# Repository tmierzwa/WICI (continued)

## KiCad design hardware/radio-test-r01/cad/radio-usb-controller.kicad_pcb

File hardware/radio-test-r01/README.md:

# WICI R01.3: kontroler w archiwum

**Status: ARCHIWUM. Kontrolera nie buduje się ani jako stanowiska, ani jako modemu; źródła pozostają do wglądu.**

W wersji 0.5 R01.3 nie jest kontrolerem stacji: STM32F103 ma za mało pamięci na stos Reticulum. Pomiary profilu P1 i próby T1–T4 wykonuje się na [stanowisku deweloperskim](../dev-bench/README.md) z płytek rozwojowych i modułów producentów, a pierwszą drukowaną płytką projektu jest płytka stacji R02 z [wymagań w specyfikacji elektroniki](../../docs/spec/elektronika.md). Z R01.3 przechodzą do R02 tylko wnioski toru RF z [warunków przed zamówieniem](przed-produkcja.md); kontrakt USB/KISS nie obowiązuje.

Przegląd elektryczny wskazał problem USB suspend: Y1 ma stale włączony zegar, więc parametry katalogowe nie gwarantują budżetu 2,5 mA przy zasilaniu z VBUS. Poprawka wymagałaby nowej rewizji CAD; po archiwizacji nie jest planowana.

Repozytorium zawiera edytowalne pliki kontrolera USB w KiCad. Tor radiowy CC1120 był osobnym modułem opartym na referencji TI; na stanowisku deweloperskim zastępuje go gotowy moduł TI CC1120EM-868-915.

| Plik | Zawartość |
|---|---|
| [Projekt KiCad](cad/radio-usb-controller.kicad_pro) | Schemat, PCB 70 × 55 mm, cztery warstwy, lokalne biblioteki |
| [Schemat](cad/radio-usb-controller.kicad_sch) | USB, STM32, zegar, EEPROM, programator, interfejs radia |
| [PCB](cad/radio-usb-controller.kicad_pcb) | Rozmieszczenie i poprowadzone połączenia |
| [BOM](bom.csv) | MPN i producenci; 39 pozycji montażowych na jeden kontroler; TP1–TP7 to pola pomiarowe |
| [Połączenia](polaczenia.md) | Numery pinów i przewód do referencji TI |
| [Uruchomienie](uruchomienie.md) | Kolejne pomiary oraz warunki przerwania próby |
| [Otwarte sprawy](przed-produkcja.md) | Przeszkody przed zamówieniem |
| [Zmiany R01.3](zmiany-R01-3.md) | Stos 1,6 mm, rewizja, MPN i zweryfikowane eksporty |
| [Paczka produkcyjna](fabrication/wici-controller-R01.3.zip) | Kandydat: Gerbery, wiercenia i pliki montażowe samego kontrolera |
| [Zmiany R01.2](zmiany-R01-2.md) | Zasilanie 0,5 mm, przelotki, otwory i bezpiecznik |
| [Wydruk 1:1](mechanika-1-do-1.pdf) | Fizyczna kontrola USB-B, SW1 i IDC; druk 100%, bez odbicia |
| [Weryfikacja](checks/status.json) | Wyniki, zakres i ograniczenia kontroli |

Kontroler: ERC 0, DRC 0, brakujących połączeń 0, różnic PCB–schemat 0. Raporty pochodzą z KiCad 10.0.6, z jawnymi regułami w pliku `.kicad_dru` i wypełnionymi polami miedzi. Kontrola zachowuje domyślne pominięcia KiCad wymienione w JSON; nie jest pełnym dowodem poprawności układu.

**Nie ma jeszcze gotowego modemu do użycia.** Nie ma firmware, zaakceptowanego zegara RF, zweryfikowanego pliku produkcyjnego RF ani wyników fizycznych prób. DRC nie sprawdza impedancji USB, dopasowania anteny, jakości lutowania ani zasięgu. Zasięg 1 km jest celem, który wymaga pomiaru.

Wygenerowano i sprawdzono paczkę Gerberów samego kontrolera R01.3. Nie sprawdzono fizycznego dopasowania złączy. Stos producenta jest zapisany w PCB; ocena impedancji USB i kwalifikacja układu pozostają otwarte. Lokalny folder `reference-private` zawiera materiały producenta i niezaakceptowaną konwersję oznaczoną `NOT-FOR-FAB`; folder nie jest częścią repozytorium.

[Odtworzenie kontroli i paczek](odtworzenie.md). [Środowisko narzędzi](../../docs/development.md).

Otwórz plik projektu w KiCad 10.0.6. Nie trzeba instalować dodatkowych bibliotek elementów. [Licencje](LICENSES.md) rozdzielają własny projekt od materiałów producentów.

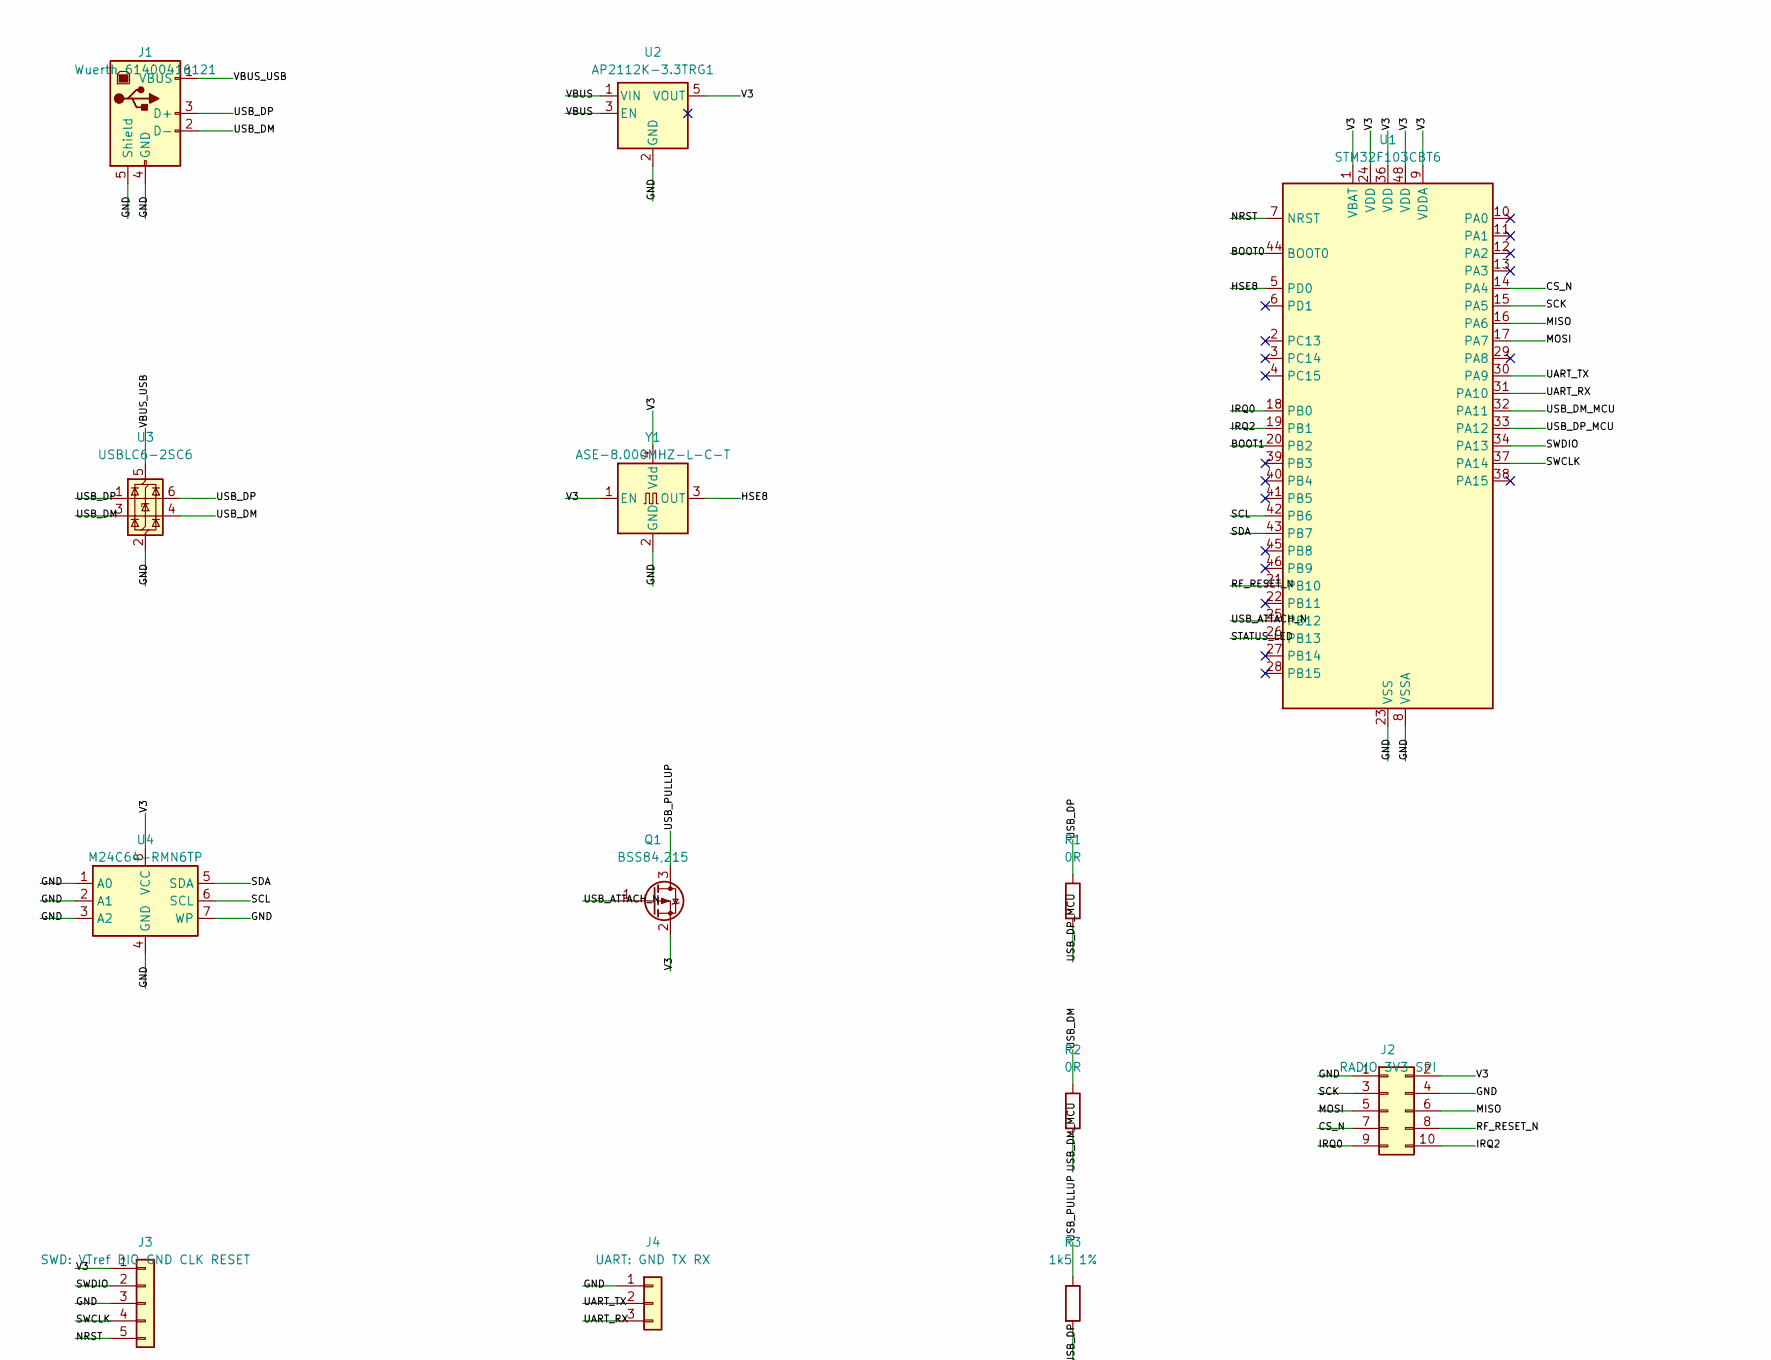
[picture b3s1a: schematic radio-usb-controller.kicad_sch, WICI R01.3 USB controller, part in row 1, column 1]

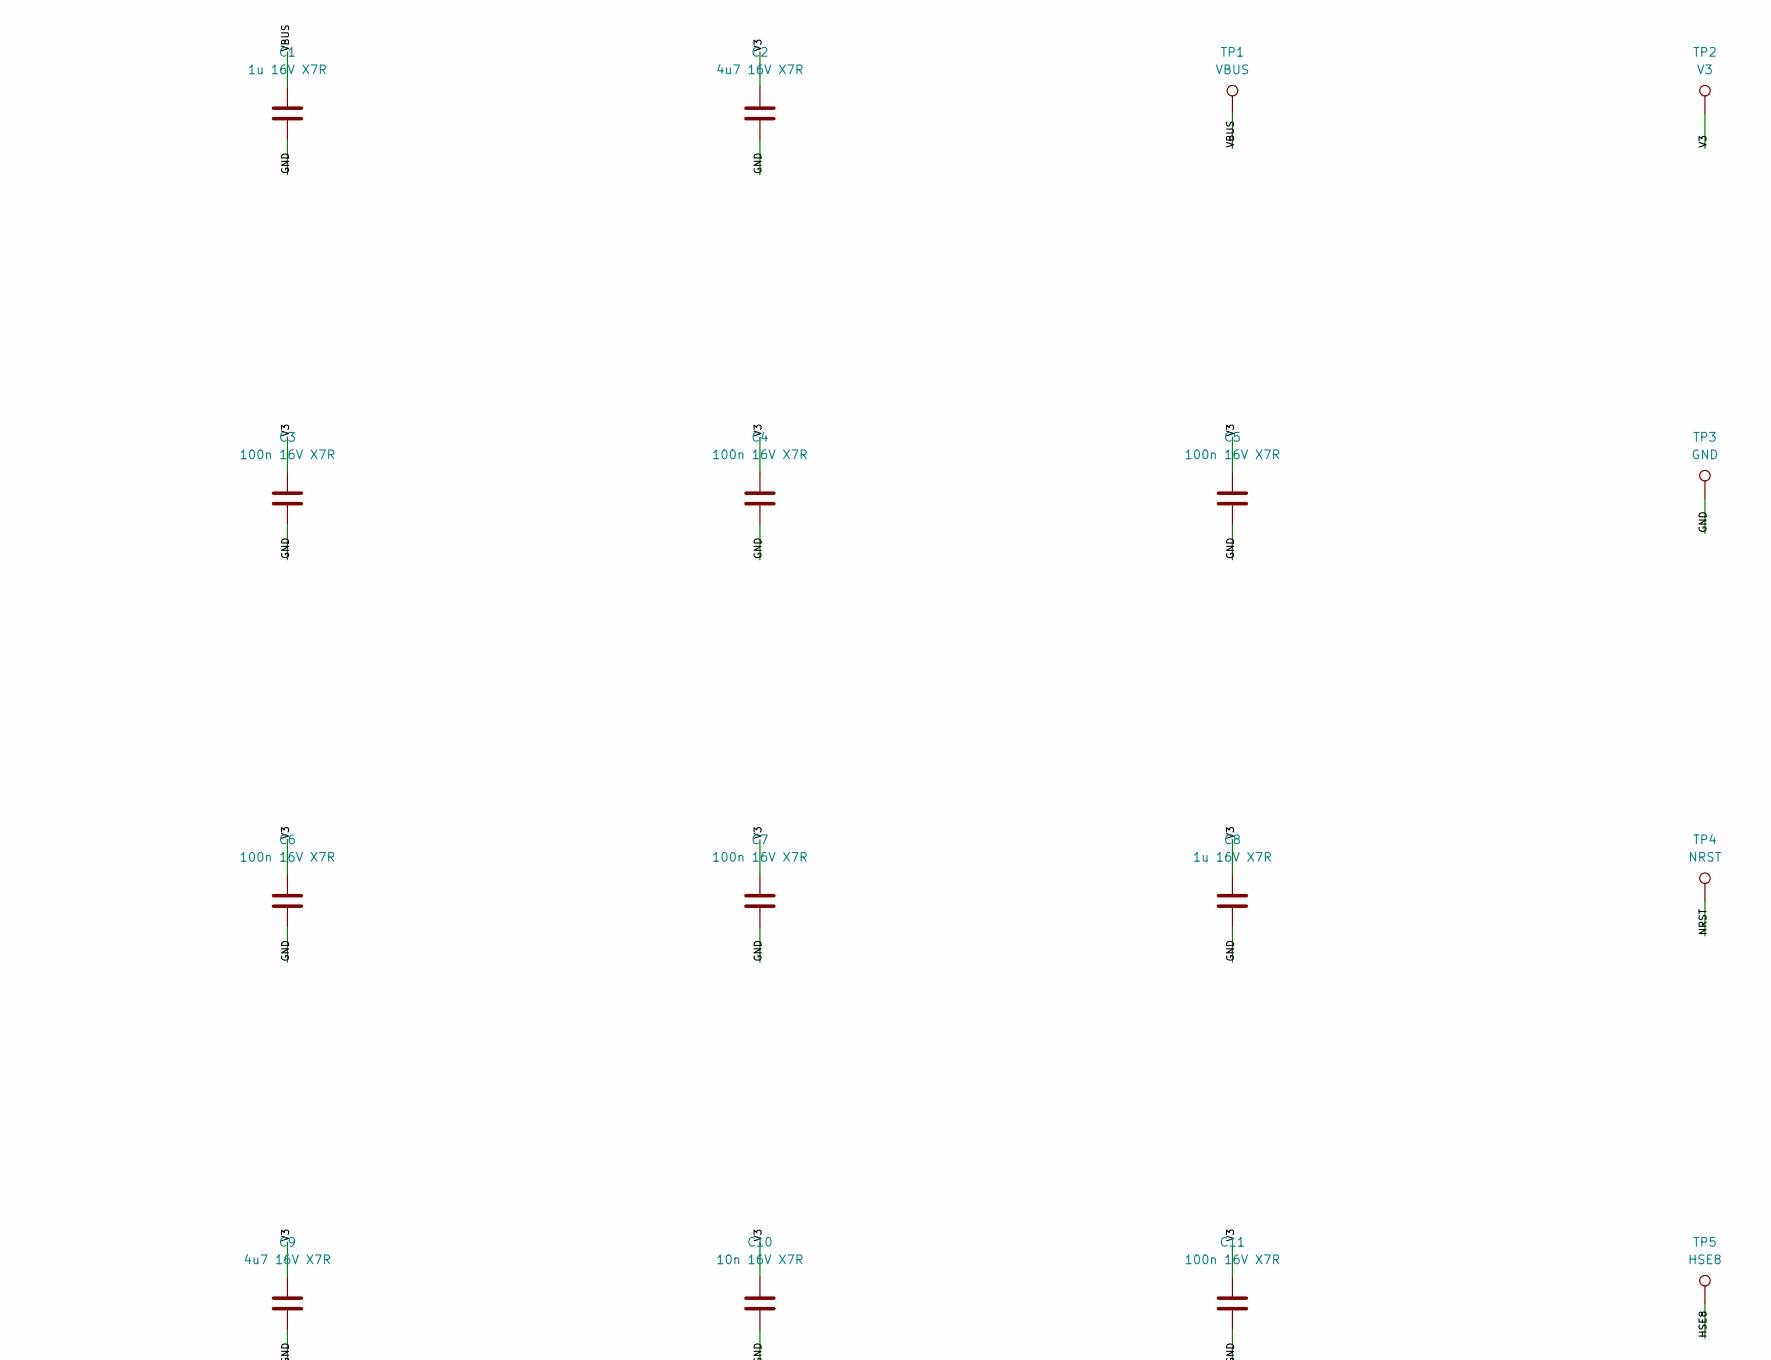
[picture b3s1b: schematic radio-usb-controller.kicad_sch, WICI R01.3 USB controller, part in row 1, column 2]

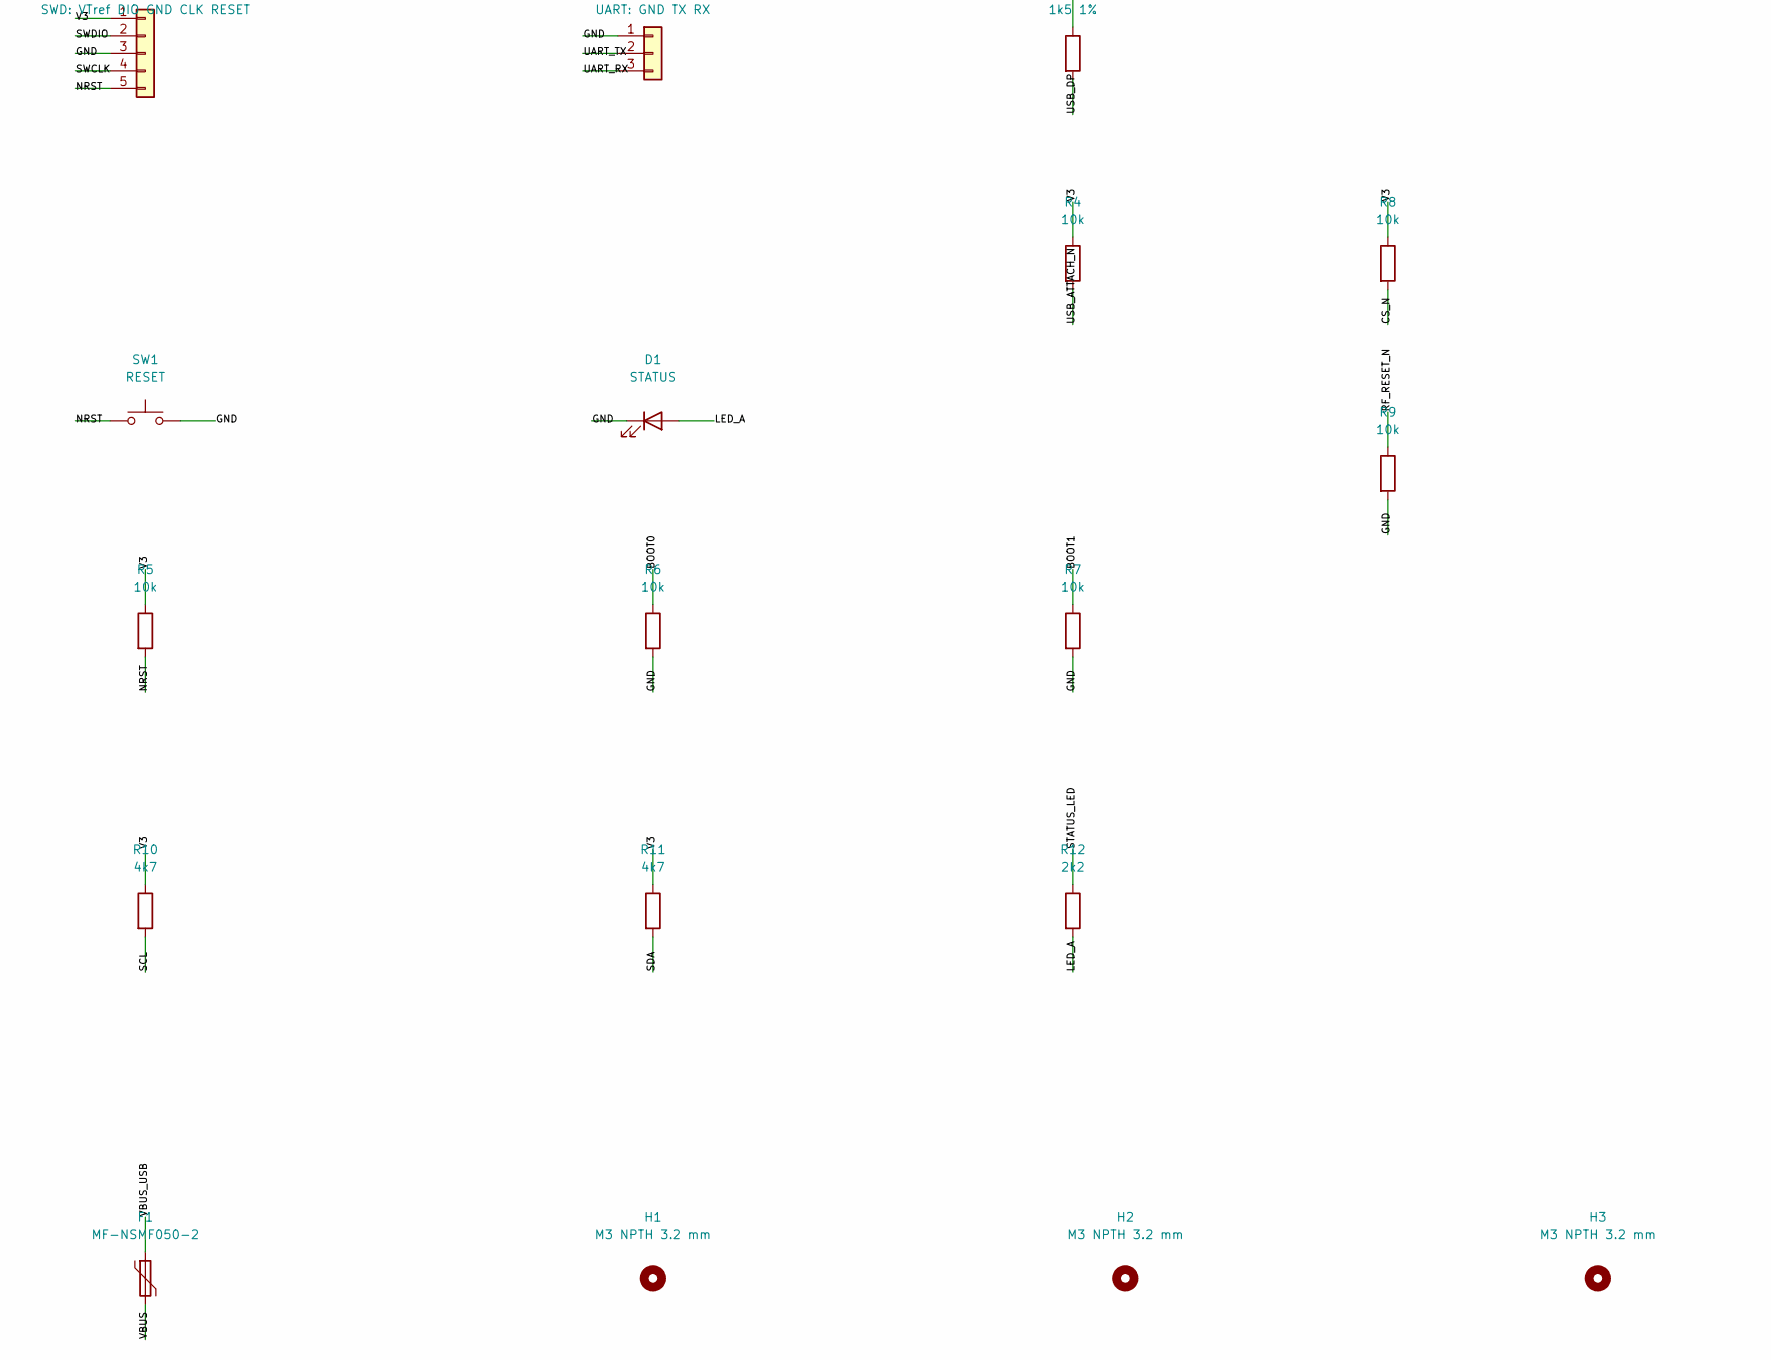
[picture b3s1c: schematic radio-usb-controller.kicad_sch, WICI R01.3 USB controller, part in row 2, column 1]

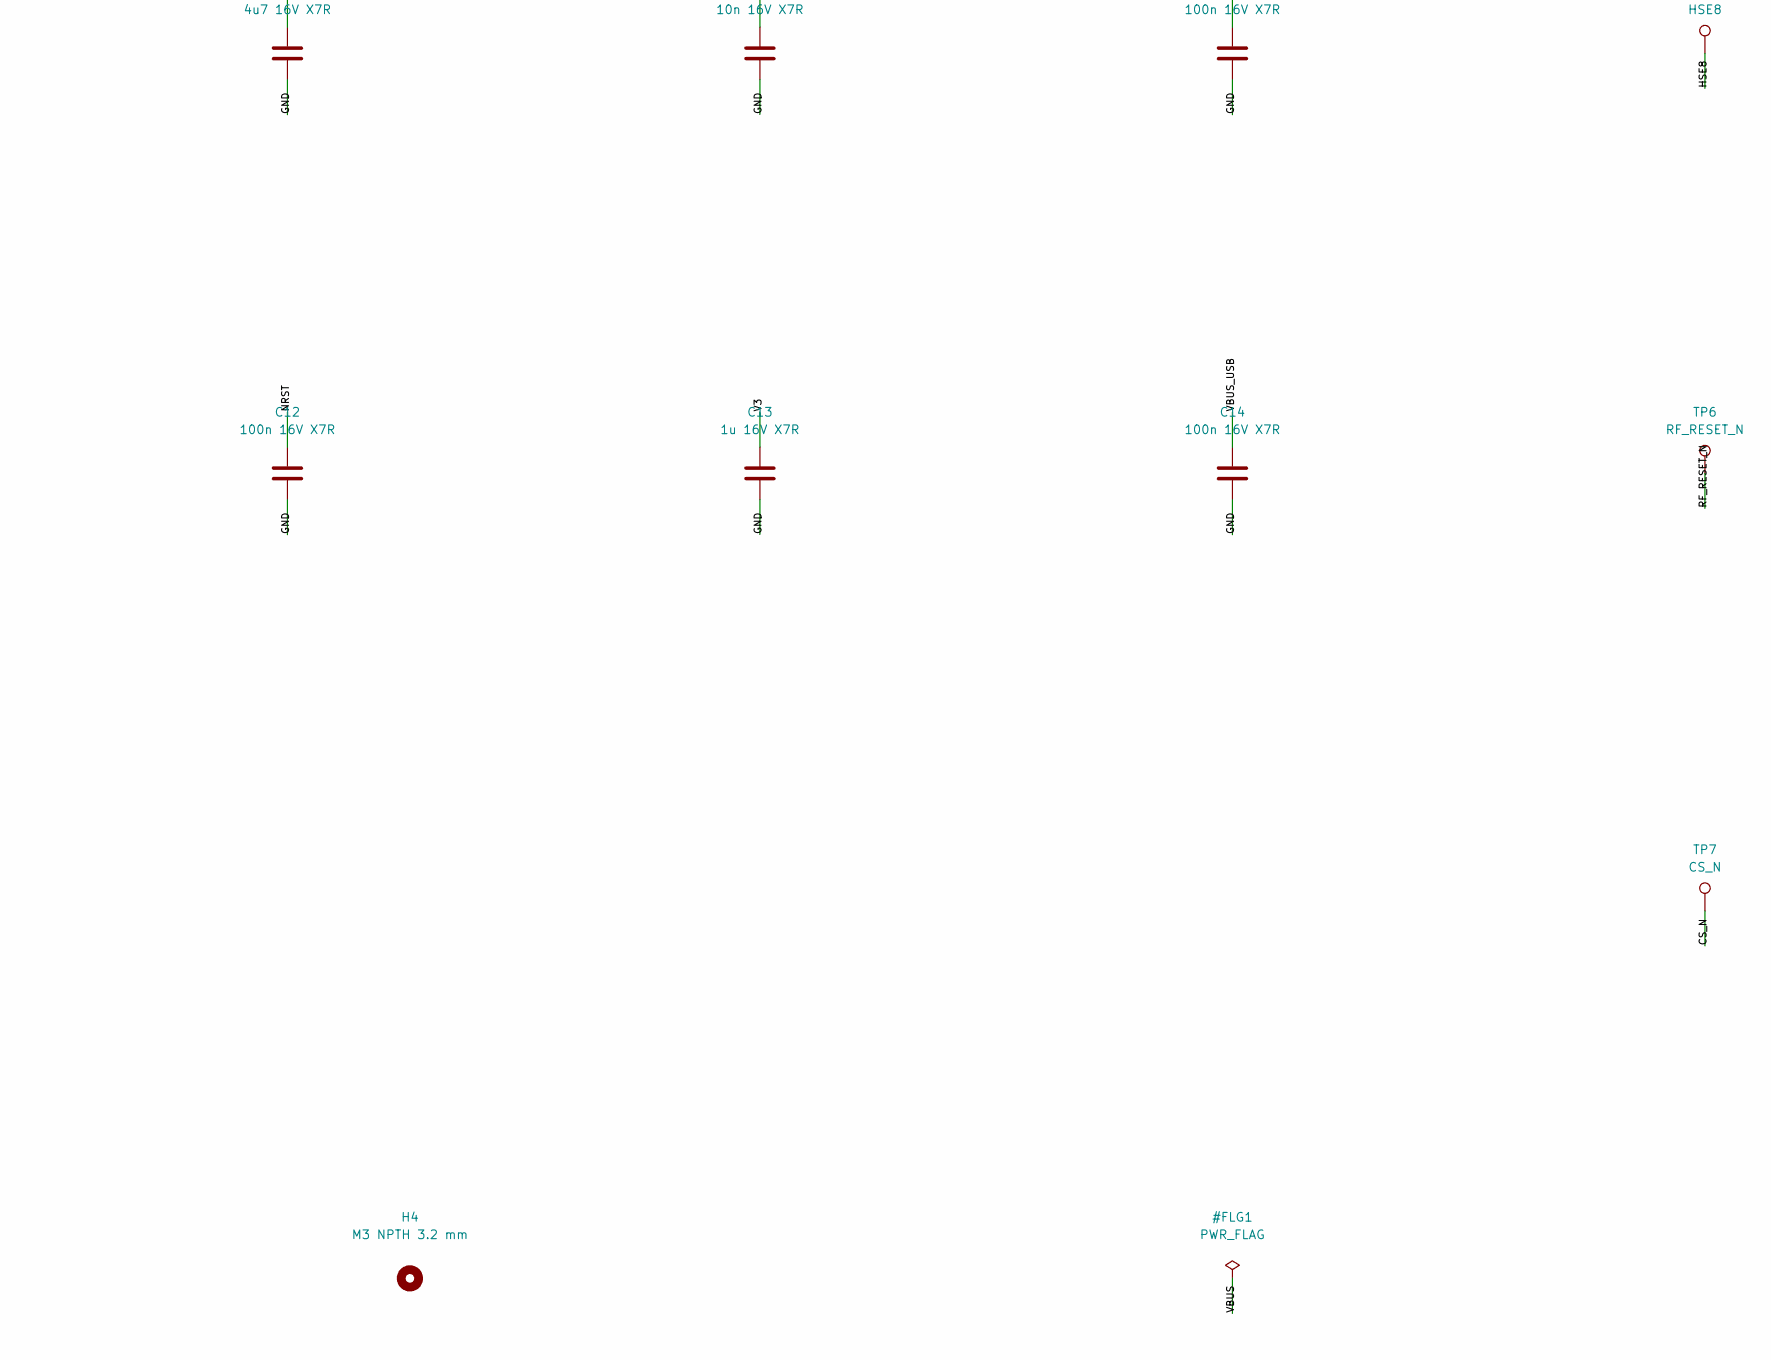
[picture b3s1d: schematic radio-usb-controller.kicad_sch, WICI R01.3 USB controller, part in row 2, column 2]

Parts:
C1, C8, C13: 1u 16V X7R; C_0805_2012Metric; MPN GRM21BR71C105KA01L
C2, C9: 4u7 16V X7R; C_0805_2012Metric; MPN GRM21BR71C475KA73L
C3, C4, C5, C6, C7, C11, C12, C14: 100n 16V X7R; C_0805_2012Metric; MPN GRM21BR71C104KA01L
C10: 10n 16V X7R; C_0805_2012Metric; MPN C0805C103K5RACTU
D1: STATUS; LED_0805_2012Metric; MPN APT2012LSECK/J3-PRV
F1: MF-NSMF050-2; PPTC_1206_1.8x1.8_Gap1.0; MPN MF-NSMF050-2
H1, H2, H3, H4: M3 NPTH 3.2 mm; MountingHole_3.2mm_M3
J1: Wuerth 61400416121; USB_B_61400416121; MPN 61400416121
J2: RADIO 3V3 SPI; IDC_61201021621; MPN 61201021621
J3: SWD: VTref DIO GND CLK RESET; PinHeader_1x05_P2.54mm_Vertical; MPN TSW-105-07-L-S
J4: UART: GND TX RX; PinHeader_1x03_P2.54mm_Vertical; MPN TSW-103-07-L-S
Q1: BSS84,215; SOT-23; MPN BSS84,215
R1, R2: 0R; R_0805_2012Metric; MPN CRCW08050000Z0EA
R3: 1k5 1%; R_0805_2012Metric; MPN CRCW08051K50FKEA
R4, R5, R6, R7, R8, R9: 10k; R_0805_2012Metric; MPN CRCW080510K0FKEA
R10, R11: 4k7; R_0805_2012Metric; MPN CRCW08054K70FKEA
R12: 2k2; R_0805_2012Metric; MPN CRCW08052K20FKEA
SW1: RESET; SW_PUSH_6mm; MPN B3F-1000
TP1: VBUS; TestPoint_Pad_D1.5mm
TP2: V3; TestPoint_Pad_D1.5mm
TP3: GND; TestPoint_Pad_D1.5mm
TP4: NRST; TestPoint_Pad_D1.5mm
TP5: HSE8; TestPoint_Pad_D1.5mm
TP6: RF_RESET_N; TestPoint_Pad_D1.5mm
TP7: CS_N; TestPoint_Pad_D1.5mm
U1: STM32F103CBT6; LQFP-48_7x7mm_P0.5mm; MPN STM32F103CBT6
U2: AP2112K-3.3TRG1; SOT-23-5; MPN AP2112K-3.3TRG1
U3: USBLC6-2SC6; SOT-23-6; MPN USBLC6-2SC6
U4: M24C64-RMN6TP; SOIC-8_3.9x4.9mm_P1.27mm; MPN M24C64-RMN6TP
Y1: ASE-8.000MHZ-L-C-T; Oscillator_SMD_Abracon_ASE-4Pin_3.2x2.5mm; MPN ASE-8.000MHZ-L-C-T

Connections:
/BOOT0: R6.1, U1.44 (BOOT0)
/BOOT1: R7.1, U1.20 (PB2)
/CS_N: J2.7, R8.2, TP7.1, U1.14 (PA4)
/GND: C1.2, C2.2, C3.2, C4.2, C5.2, C6.2, C7.2, C8.2, C9.2, C10.2, C11.2, C12.2, C13.2, C14.2, D1.1 (K), J1.4 (GND), J1.5 (Shield), J2.1, J2.4, J3.3, J4.1, R6.2, R7.2, R9.2, SW1.2, TP3.1, U1.8 (VSSA), U1.23 (VSS), U1.35 (VSS), U1.47 (VSS), U2.2 (GND), U3.2 (GND), U4.1 (A0), U4.2 (A1), U4.3 (A2), U4.4 (GND), U4.7 (WP), Y1.2 (GND)
/HSE8: TP5.1, U1.5 (PD0), Y1.3 (OUT)
/IRQ0: J2.9, U1.18 (PB0)
/IRQ2: J2.10, U1.19 (PB1)
/LED_A: D1.2 (A), R12.2
/MISO: J2.6, U1.16 (PA6)
/MOSI: J2.5, U1.17 (PA7)
/NRST: C12.1, J3.5, R5.2, SW1.1, TP4.1, U1.7 (NRST)
/RF_RESET_N: J2.8, R9.1, TP6.1, U1.21 (PB10)
/SCK: J2.3, U1.15 (PA5)
/SCL: R10.2, U1.42 (PB6), U4.6 (SCL)
/SDA: R11.2, U1.43 (PB7), U4.5 (SDA)
/STATUS_LED: R12.1, U1.26 (PB13)
/SWCLK: J3.4, U1.37 (PA14)
/SWDIO: J3.2, U1.34 (PA13)
/UART_RX: J4.3, U1.31 (PA10)
/UART_TX: J4.2, U1.30 (PA9)
/USB_ATTACH_N: Q1.1 (G), R4.2, U1.25 (PB12)
/USB_DM: J1.2 (D-), R2.1, U3.3 (I/O2), U3.4 (I/O2)
/USB_DM_MCU: R2.2, U1.32 (PA11)
/USB_DP: J1.3 (D+), R1.1, R3.2, U3.1 (I/O1), U3.6 (I/O1)
/USB_DP_MCU: R1.2, U1.33 (PA12)
/USB_PULLUP: Q1.3 (D), R3.1
/V3: C2.1, C3.1, C4.1, C5.1, C6.1, C7.1, C8.1, C9.1, C10.1, C11.1, C13.1, J2.2, J3.1, Q1.2 (S), R4.1, R5.1, R8.1, R10.1, R11.1, TP2.1, U1.1 (VBAT), U1.9 (VDDA), U1.24 (VDD), U1.36 (VDD), U1.48 (VDD), U2.5 (VOUT), U4.8 (VCC), Y1.1 (EN), Y1.4 (Vdd)
/VBUS: C1.1, F1.2, TP1.1, U2.1 (VIN), U2.3 (EN)
/VBUS_USB: C14.1, F1.1, J1.1 (VBUS), U3.5 (VBUS)

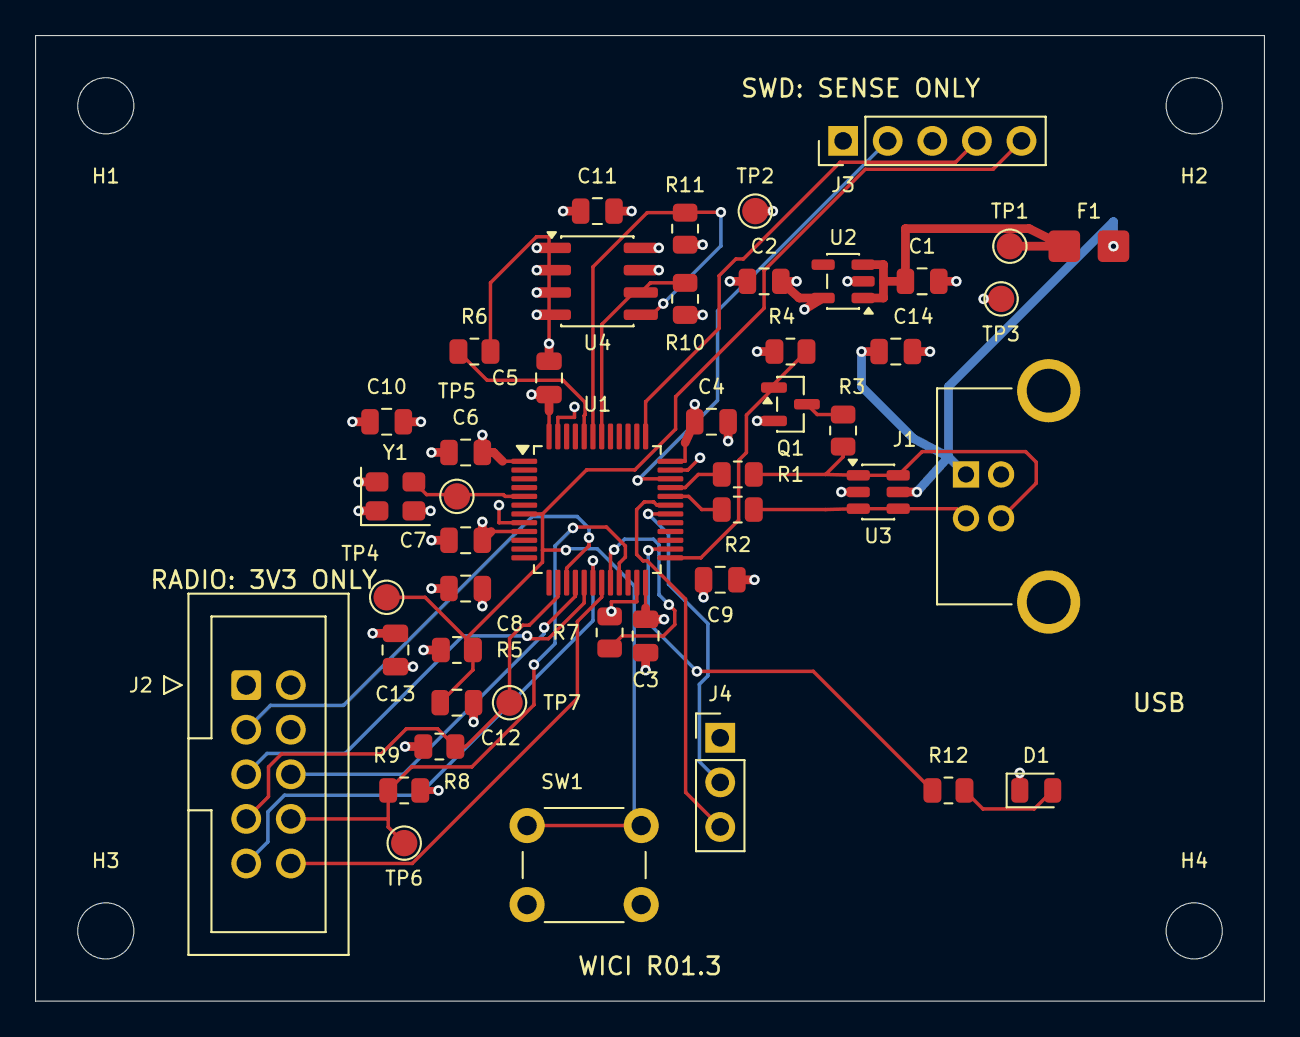
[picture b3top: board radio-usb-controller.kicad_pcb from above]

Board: 4 copper layers, 70.0 x 55.0 mm, 50 parts (0 on the bottom side), 29 nets.

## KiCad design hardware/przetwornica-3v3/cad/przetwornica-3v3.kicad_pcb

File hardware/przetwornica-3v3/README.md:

# Płytka testowa przetwornicy 3,3 V (LTC3115-1)

Mała płytka do pomiaru sprawności przetwornicy z [projektu zasilania](../r02/zasilanie.md) przed schematem v2 (Z11). Układ i wartości elementów są te same co w projekcie: 3,3 V, 750 kHz, dławik 15 µH, dzielnik 1 MΩ / 432 kΩ, kompensacja typu III.

Dlaczego pomiar jest potrzebny:

- karta LTC3115-1 (rew. E) ma krzywe sprawności tylko dla 5 V, a płytka ewaluacyjna DC1687B (około 230 USD) też jest ustawiona na 5 V i ma krzywe od 100 mA;
- model LTspice producenta zawyża sprawność o 8–25 punktów względem krzywych z karty, więc się do tego nie nadaje;
- z krzywych dla 5 V wychodzi dla 3,3 V przy 30–60 mA w Burst Mode około 74–83%. Przy dolnej granicy model energii daje około 47 h, czyli mniej niż W23 (48 h).

## Układ

| Element | Wartość | Połączenie |
|---|---|---|
| U1 | LTC3115EFE-1 (TSSOP-20 z padem termicznym) | piny 1, 5, 6, 10, 11, 20 i pad: GND; 12 i 14: VCC; 13 i 17: VIN; 4: VOUT |
| L1 | 15 µH, Bourns SRP1038A-150M | SW2 (pin 3) – SW1 (pin 18) |
| C1, C2 | 10 µF 50 V X7R 1210 | VIN – GND |
| C3, C4 | 22 µF 16 V X5R 1210 | VOUT – GND |
| C5 / C6 | 100 nF 16 V 0402 | BST1 (16) – SW1 / BST2 (15) – SW2 |
| C7 | 100 nF | VIN (13) – GND |
| C8 | 10 µF 25 V 0805 (przy 4,45 V zostaje około 6 µF, karta wymaga ≥4,7 µF) | VCC – GND |
| C12 | 47 µF 25 V elektrolityczny, przewlekany | VIN – GND przy zacisku: pojemność na przewody zasilacza i amperomierz (karta s. 11) |
| R9 / R10 | 10 MΩ / 100 kΩ | RUN – GND / PWM/SYNC – GND: stan niski bez zworki |
| R1 | 47,5 kΩ | RT (9) – GND: 750 kHz |
| R2 / R3 | 1 MΩ / 432 kΩ | VOUT – FB (8) – GND: 3,31 V |
| C9 | 82 pF (C_POLE) | FB – VC (7) |
| C10 + R4 | 3,9 nF + 20 kΩ szeregowo (C_FB, R_FB) | FB – VC |
| C11 + R5 | 82 pF + 20 kΩ szeregowo (C_FF, R_FF) | FB – VOUT |
| R6, R7 | 110 Ω 1 W 2512, zworki JP1, JP2 | VOUT – GND: po 30 mA |
| R8 | 22 Ω 1 W 2512, zworka JP3 | VOUT – GND: 150 mA |
| JP4 | listwa 1×3: VIN / RUN / GND | zworka 1–2 pracuje, 2–3 wyłączenie |
| JP5 | listwa 1×3: VCC / PWM/SYNC / GND | zworka 1–2 PWM, 2–3 Burst Mode; środkowy pin przyjmuje zegar SYNC |
| J1, J2 | zaciski Phoenix 5,08 mm | wejście VIN i wyjście VOUT (obciążenie zewnętrzne) |
| TP1–TP4 | pola pomiarowe | VIN i GND przy C1, VOUT i GND przy C3 |

R9 ma 10 MΩ, żeby prawie nie zmieniał poboru: przy RUN = VIN dokłada VIN / 10 MΩ, czyli 0,6 µA przy 6 V i 1,3 µA przy 12,8 V. R9 trzyma układ wyłączony przy starcie bez zworki. Pracującego układu nie wyłączy, bo RUN wystawia wtedy 0,5 µA histerezy (karta s. 11), więc wyłączenie to zawsze zworka JP4 na 2–3. R10 (100 kΩ) pobiera prąd tylko w PWM i trzyma pin w stanie niskim mimo sąsiedztwa miedzi SW1.

Płytka ma 4 warstwy, wymiary 56 × 48 mm, otwory M3 w rogach. Rozmieszczenie idzie za rysunkiem 17 karty:

- dławik jest nad układem, SW2 i wyjście po lewej, SW1 i wejście po prawej;
- połączenia BST biegną warstwą In2;
- In1 jest ciągłą masą;
- FB, VC i RT są pod układem, z dala od węzłów przełączania.
- Przelotki RUN i PWM/SYNC leżą w miedzi SW, tak jak na rysunku.
- Pas VIN od pinu 17 ma szerokość pinu, a kondensator wejściowy stoi za kolumną SW1. Przelotki BST nie zwężają tego przejścia, a masa kondensatorów schodzi do In1 przelotkami tuż przy padach.
- Pad termiczny ma pastę w czterech okienkach między przelotkami (około 40% powierzchni), bez pasty nad otworami.

Przebieg SW mierzy się sondą na wystających padach dławika.

## Pliki

| Plik | Zawartość |
|---|---|
| `tools/build.py` | generator płytki (pcbnew), edytowalne źródło; własne footprinty U1 (pad termiczny wg rysunku FE20 z karty) i L1 (wg zalecanego padu Bourns) |
| `tools/export.sh` | generator, DRC, Gerbery i wiercenia, ZIP dla JLC |
| `cad/` | płytka KiCad 10.0.6 |
| `checks/drc.json` | raport DRC; jedyne ostrzeżenia dotyczą własnych footprintów spoza biblioteki |
| [BOM](bom.csv) | części z kodami LCSC |
| `fabrication/` | `przetwornica-3v3-gerber.zip`, `jlc-bom.csv`, `jlc-cpl.csv` |

Generator sprawdza też odstęp co najmniej 2,5 mm między padami SMD i przewlekanymi, jak dla płytki v2.

## Zamówienie (JLCPCB)

2026-10-31 zamówiono 2 sztuki z montażem SMD i THT. Pliki zamówienia wskazuje tag [`hw-przetwornica-3v3-r1`](https://github.com/tmierzwa/WICI/tree/hw-przetwornica-3v3-r1/hardware/przetwornica-3v3) (SHA-256 `przetwornica-3v3-gerber.zip`: `32fc0276…83f72c4`). Zmiany w tym katalogu po tym tagu nie dotyczą zamówionych płytek.

- PCB: 4 warstwy, 1,6 mm, plik `fabrication/przetwornica-3v3-gerber.zip`, 5 sztuk; przelotki zakryte maską (tented).
- Montaż: tylko strona górna, SMD i THT z `jlc-bom.csv` i `jlc-cpl.csv` (2 sztuki wystarczą). W wycenie sprawdza się, że części przewlekane (C12, JP1–JP5, J1, J2) są w montażu, a nie pominięte. Kody LCSC i stan sprawdzono 2026-10-31: wszystkie pozycje są w magazynie JLC, ale U1 (C580689) ma tylko 25 sztuk, więc stan sprawdza się ponownie przy zamówieniu.
- W podglądzie rozmieszczenia sprawdza się:
  - U1: pin 1 przy znaczku na sitodruku, w lewym górnym rogu. CPL dodaje +270° względem KiCad, bo footprint JLC tej części ma rzędy padów poziomo;
  - L1: wyprowadzenia na padach po lewej i prawej stronie. Model JLC może być obrócony o 90°; wtedy poprawia się obrót w podglądzie;
  - JP1–JP5: każda listwa stoi pionowo nad swoimi otworami. CPL obraca listwy o 90° względem KiCad, bo tak leżą modele JLC (podgląd z 2026-10-31);
  - C12: biegun + na kwadratowym padzie (VIN);
  - J1 i J2: wejście przewodu na zewnątrz, w stronę krawędzi płytki.
- Zworki nie mają footprintu, więc nie ma ich w BOM i CPL: 5 sztuk 2,54 mm (np. BOOMELE C5305 z LCSC) kupuje się osobno albo bierze z zapasu po L0.

## Pomiar

**Biegunowość zacisków** (znaki „+” i „−” na sitodruku przy końcach zacisków): J1 (VIN) ma GND u góry i + na dole, J2 (VOUT) ma + u góry i GND na dole, gdy napis „WICI 3V3” jest na dole płytki i da się go czytać. Płytka nie ma ochrony przed odwrotnym podłączeniem, więc zamiana przewodów zasilacza niszczy U1. Pierwsze włączenie robi się z ograniczeniem prądu zasilacza 100–200 mA.

Przyrządy:

- zasilacz 0–15 V;
- multimetr A w szereg na wejściu, zakres mA, a do prądu wyłączenia µA;
- multimetr V na polach pomiarowych.

Napięcie wejścia mierzy się na TP1 (za amperomierzem), więc spadek na amperomierzu nie wchodzi do wyniku. Odczyt prądu z zasilacza (zwykle co 1 mA) jest przy 20 mA za mało dokładny.

Prąd wyjścia najdokładniej mierzy się amperomierzem wpiętym w miejsce zworki JP1–JP3 (piny listwy). Wtedy tolerancja rezystora i jego nagrzewanie nie wchodzą do wyniku, a do zworki potrzebny jest trzeci multimetr albo przekładanie przewodów. Gdy amperomierza brak, prąd liczy się z napięcia i rezystancji zmierzonej przed włączeniem, z odjęciem rezystancji przewodów multimetru.

1. **Wyłączenie:** JP4 w pozycji 2–3, VIN 6,0 V i 12,8 V. Mierzy się prąd wejścia (karta podaje 3 µA typowo, 10 µA najwyżej).
2. **Bez obciążenia:** JP4 1–2, JP5 2–3 (Burst Mode), wszystkie zworki obciążeń zdjęte. Mierzy się prąd wejścia przy 6,0 V i 12,8 V. Wynik obejmuje 2,3 µA dzielnika FB i prąd R9 (0,6/1,3 µA).
3. **Obciążenia:** dla VIN 6,0 V i 12,8 V, a dodatkowo 4,0 V (koniec ogniw) i 7,3 V (świeże ogniwa), mierzy się VIN (TP1), IIN i VOUT (TP3):

   | Tryb (JP5) | Zworki | Prąd wyjścia |
   |---|---|---|
   | Burst Mode (2–3) | JP1 | 30 mA |
   | Burst Mode (2–3) | JP1 + JP2 | 60 mA |
   | PWM (1–2) | JP1 + JP2 | 60 mA |
   | PWM (1–2) | JP3 | 150 mA |

   Każdy punkt odczytuje się po minucie. Sprawność: η = (VOUT · IOUT) / (VIN · IIN). Przy liczeniu prądu z rezystancji IOUT = VOUT / R, a przy JP1 + JP2 rezystory liczy się równolegle. Burst Mode obsługuje zwykle poniżej 50 mA, więc 150 mA mierzy się tylko w PWM.

Wyniki zapisuje się w `hardware/r02/checks/` (osoba, data, przyrządy, numer płytki) i wpisuje do Z11 [projektu zasilania](../r02/zasilanie.md) oraz do modelu energii.

Licencje według [LICENSE.md](../../LICENSE.md): projekt płytki i pliki produkcyjne CERN-OHL-P-2.0, skrypty MIT, dokumentacja CC-BY-4.0.

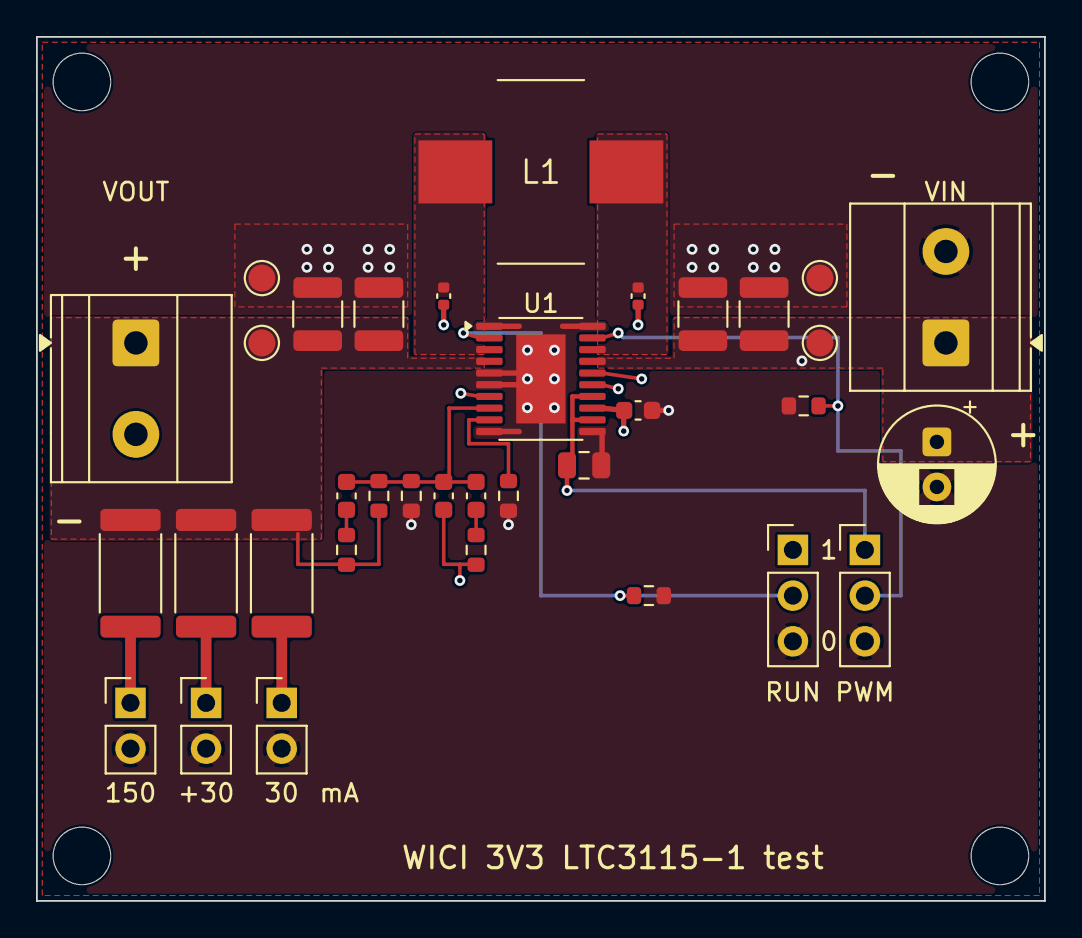
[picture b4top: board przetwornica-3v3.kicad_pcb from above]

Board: 4 copper layers, 56.0 x 48.0 mm, 39 parts (0 on the bottom side), 18 nets.

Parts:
C1, C2: 10uF 50V X7R; C_1210_3225Metric
C3, C4: 22uF 16V X5R; C_1210_3225Metric
C5, C6: 100nF 16V; C_0402_1005Metric
C7: 100nF; C_0603_1608Metric
C8: 10uF 25V X5R; C_0805_2012Metric
C9, C11: 82pF C0G; C_0603_1608Metric
C10: 3.9nF; C_0603_1608Metric
C12: 47uF 25V; CP_Radial_D6.3mm_P2.50mm
H: MountingHole_3.2mm_M3
H#2, H#3, H#4: MountingHole_3.2mm_M3
J1: VIN; TerminalBlock_Phoenix_MKDS-1,5-2-5.08_1x02_P5.08mm_Horizont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
J2: VOUT; TerminalBlock_Phoenix_MKDS-1,5-2-5.08_1x02_P5.08mm_Horizont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
JP1, JP2, JP3: zworka; PinHeader_1x02_P2.54mm_Vertical
JP4: RUN; PinHeader_1x03_P2.54mm_Vertical
JP5: PWM/SYNC; PinHeader_1x03_P2.54mm_Vertical
L1: 15uH; L_Bourns_SRP1038A
R1: 47.5k 1%; R_0603_1608Metric
R2: 1M 1%; R_0603_1608Metric
R3: 432k 1%; R_0603_1608Metric
R4, R5: 20k 1%; R_0603_1608Metric
R6, R7: 110R 1W 1%; R_2512_6332Metric
R8: 22R 1W 1%; R_2512_6332Metric
R9: 10M 1%; R_0603_1608Metric
R10: 100k 1%; R_0603_1608Metric
TP1, TP2, TP3, TP4: TestPoint_Pad_D1.5mm
U1: LTC3115EFE-1#PBF; LTC3115-1_FE20_CA

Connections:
BST1: C5.1, U1.16
BST2: C6.1, U1.15
FB: C9.2, C10.2, C11.2, R2.2, R3.2, U1.8
GND: C1.2, C2.2, C3.2, C4.2, C7.2, C8.2, C12.2, J1.2, J2.2, JP1.2, JP2.2, JP3.2, JP4.3, JP5.3, R1.1, R3.1, R9.2, R10.1, TP2.1, TP4.1, U1.1, U1.5, U1.6, U1.10, U1.11, U1.20, U1.21
NC: C10.1, R4.2
NF: C11.1, R5.2
OBC_JP1: JP1.1, R6.1
OBC_JP2: JP2.1, R7.1
OBC_JP3: JP3.1, R8.1
PWM: JP5.2, R10.2, U1.19
RT: R1.2, U1.9
RUN: JP4.2, R9.1, U1.2
SW1: C5.2, L1.2, U1.18
SW2: C6.2, L1.1, U1.3
VC: C9.1, R4.1, U1.7
VCC: C8.1, JP5.1, U1.12, U1.14
VIN: C1.1, C2.1, C7.1, C12.1, J1.1, JP4.1, TP1.1, U1.13, U1.17
VOUT: C3.1, C4.1, J2.1, R2.1, R5.1, R6.2, R7.2, R8.2, TP3.1, U1.4
